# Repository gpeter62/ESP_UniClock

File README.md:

# ESP_UniClock v3.1

**A universal Wi-Fi clock firmware for ESP8266 / ESP32 — one codebase, 60+ different physical builds.**

Drive Nixie, VFD (vacuum fluorescent), Numitron, LED-segment, LED-matrix or NeoPixel "word clock"
displays from a single Arduino sketch. Which physical hardware you're building is selected entirely
in one file (`clocks.h`) — no code changes needed for a new build, just a new configuration block.

License: GPL-3.0-or-later (see the header of `ESP32_UniClock2.ino`) · Platforms: ESP8266, ESP32 ·
Language: C++ (Arduino)

---

## Table of contents

- [Features](#features)
- [Supported display drivers](#supported-display-drivers)
- [Optional components](#optional-components)
- [Screenshots](#screenshots)
- [Requirements](#requirements)
- [Getting started](#getting-started)
- [Configuration](#configuration-clocksh)
- [Developer documentation](#developer-documentation)
- [Schematics & PCB designs](#schematics--pcb-designs)
- [Manuals](#manuals)
- [External libraries](#external-libraries-bundled-in-libraries)
- [Known issues](#known-issues)
- [License](#license)
- [Author & support](#author--support)

---

## Features

- Works with any ESP8266 or ESP32 based module, via the Arduino IDE
- 1, 4, 6, 8 or 12 clock digits (tubes), depending on the build
- Time sync via Wi-Fi (NTP), GPS, or a DS3231 RTC chip — with automatic fallback between sources
- Wi-Fi in both infrastructure (STA) and standalone access-point (AP) modes, configured through a
  built-in responsive web UI (see [Screenshots](#screenshots))
- Temperature / humidity / barometric-pressure / ambient-light sensor support (see
  [Optional components](#optional-components))
- Adjustable day/night brightness, with optional automatic dimming from an ambient light sensor
- Radar or PIR motion sensor support to power tubes off when no one's around
- 8 tube-transition animation modes (including a random-pick mode)
- Full-color WS2812 (NeoPixel) tube backlighting with multiple animation effects
- Alarm function with buzzer and light
- Cathode/tube-life protection ("anti-poisoning") cycling
- Home Assistant integration via MQTT, including a master/slave mode so several clocks can share one
  physical sensor
- OTA firmware updates from the web UI
- Single-file hardware setup via `clocks.h` — no other source changes needed for a new physical build

## Supported display drivers

| Driver chip / scheme | Display type | Driver file(s) |
|---|---|---|
| SN74141 / 7441 / K155ID1 (BCD decoder), multiplexed | Nixie | `multiplex74141.ino` (8266), `multiplex74141_ESP32.ino` |
| SN74141, non-multiplexed (one decoder per tube) | Nixie | `no_multiplex74141.ino` (8266), `no_multiplex_ESP32.ino` |
| SN74141 + PCF8574 I²C port expander | Nixie | `pcf_multiplex74141.ino` |
| MAX6921 (20-ch. HV shift register) | VFD | `MAX6921.ino` (8266), `MAX6921_ESP32.ino` |
| HV5122 (32-ch. HV shift register, cascaded ×2) | Nixie | `HV5122new.ino` |
| PT6311 / PT6355 (smart VFD controller, on-chip scan) | VFD | `PT6311.ino`, `PT6355.ino` |
| SN75512 / SN75518 (HV shift register) | VFD | `SN75512.ino`, `SN75518.ino` |
| MM5450 (34-ch. LED driver) | LED 7-segment | `MM5450.ino` |
| MAX7219 / compatible | LED matrix / 7-segment | `MAX7219CNG.ino` |
| CD4511 / 74HC4511 (BCD→7-segment) | Numitron | `Numitron_4511N.ino` |
| 4× 74HC595 + optocouplers | Custom segment displays | `ZM1500.ino` |
| CD4543 + CD4028 (BCD→7-segment / BCD→decimal) | LED 7-segment | `mulev2.ino` ("Mule V2" board) |
| VQC10 (5×7 dot-matrix element) | Dot-matrix, full ASCII | `VQC10.ino` |
| WS2812 LED matrix behind an acrylic panel | "Word clock" (spells the time; EN/DE/HU) | `wordclock.ino` |
| — | Single-tube variant | `1tube.ino` |
| — | Sensor-only "clock" (no display) | `dummy.ino` |

Only one driver is compiled into any given firmware image — see [Configuration](#configuration-clocksh).

## Optional components

- DS18B20 temperature sensor (1 or 2 sensors on one bus)
- DHT11 / DHT22 temperature+humidity sensor
- BME280 / BMP280 / AHT10-AHT20 / SHT21 temperature/humidity/pressure sensor on I²C
- BH1750 ambient-light sensor on I²C
- Home Assistant integration via an MQTT client (with master/slave sensor sharing across clocks)
- DS3231 RTC module, settable via Wi-Fi or manually with pushbuttons
- Radar or PIR motion sensor
- GPS module for time sync in standalone (no-internet) setups
- WS2812 addressable LEDs for tube backlighting — fixed color or multiple animated effects
- Plain 3-pin PWM RGB backlighting (alternative to addressable LEDs, on boards with limited GPIO)
- User-defined GPIO pin numbers for every digit/segment/sensor/button

## Screenshots

- Web configuration UI: [`Webpage.jpg`](Webpage.jpg), [`Uniclock_v2 .png`](<Uniclock_v2 .png>)
- Photos of physical builds: [`photos/`](photos)
- PCB renders: [`PCB_available/`](PCB_available)

## Requirements

| Tool | Tested version |
|---|---|
| [Arduino IDE](https://www.arduino.cc/en/software) | **1.8.19** |
| ESP32 board package (`esp32` by Espressif Systems, via Boards Manager) | **2.0.17** |
| ESP8266 board package (`esp8266` by ESP8266 Community, via Boards Manager) | any recent 2.6.x–3.x (both are detected and handled at compile time, see `ESP32_UniClock2.ino`) |

> ⚠️ **Board package version matters.** This firmware has only been verified against **Arduino IDE
> 1.8.19** with the **ESP32 board package v2.0.17**. Newer Arduino IDE releases (2.x) or newer/older
> ESP32 core versions may require code changes (the ESP32 Arduino core's API — WiFi, LEDC/PWM, timer,
> and SPIFFS/LittleFS calls in particular — has changed across major versions). If you hit compile
> errors on a different toolchain version, try matching the tested versions above first before filing
> an issue.

## Getting started

1. **Download/clone this repository.**
2. **Install the libraries.** Unzip every archive in [`libraries/`](libraries) into your Arduino
   `libraries` folder (usually `Documents\Arduino\libraries` on Windows), **and rename this project's
   own folder to `ESP32_UniClock2`** — the sketch expects that exact folder name.
3. **Install the Boards Manager packages** for ESP8266 and/or ESP32 (see
   [Requirements](#requirements) for the tested versions).
4. **Pick (or write) your clock configuration** in [`clocks.h`](clocks.h) — see
   [Configuration](#configuration-clocksh) below.
5. **Select your board** in the Arduino IDE (`Tools → Board`) and the matching serial port.
6. **Upload the sketch** (`ESP32_UniClock2.ino`) as usual.
7. **Upload the web UI files to flash storage.** The files in [`data/`](data) (the config web page's
   HTML/CSS/JS) must be uploaded separately to SPIFFS/LittleFS using the filesystem-upload plugin —
   installers are bundled in [`SPIFFS uploaders/`](<SPIFFS uploaders>), or see:
   - [ESP8266 filesystem uploader tutorial](https://randomnerdtutorials.com/install-esp8266-filesystem-uploader-arduino-ide)
   - [ESP32 filesystem uploader tutorial](https://randomnerdtutorials.com/install-esp32-filesystem-uploader-arduino-ide)
8. **First boot**: if no Wi-Fi is configured, the clock starts its own access point (`192.168.4.1`) —
   connect to it and set your Wi-Fi/clock options from the web UI.

## Configuration (`clocks.h`)

All hardware setup lives in one file. Near the top, uncomment exactly **one** `#define CLOCK_NN` line
to select your build; every other line in that list must stay commented out. Each `CLOCK_NN` block then
defines the driver chip, GPIO pin assignments, and which optional features (sensors, RTC, GPS,
backlight, alarm, etc.) that specific build uses. To add a new physical build, copy the block closest
to your hardware, give it an unused number, and adjust the pins/options.

See [`docs/DEVELOPER_GUIDE.md`](docs/DEVELOPER_GUIDE.md) for the full breakdown of how `clocks.h`
drives the rest of the firmware.

## Developer documentation

This repository includes a full developer-documentation set (added during a 2026 code review pass):

- [`docs/DEVELOPER_GUIDE.md`](docs/DEVELOPER_GUIDE.md) — full architecture write-up: build model, the
  common driver interface, the core program's structure, the web admin API, and a complete driver catalog.
- [`docs/CODE_REVIEW.md`](docs/CODE_REVIEW.md) — file-by-file findings: bugs (fixed and open),
  optimization suggestions, and known limitations.
- [`docs/PROGRESS.md`](docs/PROGRESS.md) — status log of the review/documentation effort itself.

Every `.ino`/`.h` file in the project also has inline comments explaining the non-obvious hardware
protocol details, timing behavior, and known caveats of that specific driver.

## Schematics & PCB designs

See [`schematics/`](schematics) for KiCad-exported PCB/schematic PDFs, including:
- ESP32 clock, 6× IV-11 VFD tubes
- ESP32 clock, 6× Z573M/Z574M Nixie tubes
- ESP8266 Numitron clock, 4× IV-16 tubes
- ...and many more (ESP32 mainboard + interchangeable tube-driver daughterboards, HV5122-based flat
  panel builds, ESP8266 variants, etc.)

## Manuals

- UniClock Manual — English: [DOCX](<UniClock Manual ENG v3.1.docx>) · [PDF](<UniClock Manual ENG v3.1.pdf>)
- UniClock kézikönyv — Magyar: [DOCX](<UniClock Manual HUN v3.1.docx>) · [PDF](<UniClock Manual HUN v3.1.pdf>)

## External libraries (bundled in `libraries/`)

Core: `Time`, `Timezone`, `NTPClient`, `ESPAsyncWebServer`, `ESPAsyncTCP` (8266) / `AsyncTCP-ESP32`
(ESP32), `ESPAsyncWiFiManager`, `ArduinoJson`, `ESP32httpUpdate`, `EspSoftwareSerial`.

Optional (only needed for the sensors/features you enable): `Rtc_by_Makuna` (DS3231), `TinyGPSPlus`,
`NeoPixelBus_by_Makuna` (WS2812), `OneWire` + `DallasTemperature` (DS18B20), `DHT_sensor_library`,
`Adafruit_BME280_Library`, `Adafruit_BMP280_Library`, `Adafruit_AHTX0`, `Adafruit_BusIO`,
`Adafruit_Unified_Sensor`, `SHT21`, `BH1750`, `PubSubClient` + `arduino-home-assistant` (MQTT/Home
Assistant), `Samsung_16LF01_VFD`.

## Known issues

See [`docs/CODE_REVIEW.md`](docs/CODE_REVIEW.md) for the complete, current list. Most notably:
`mqtt.ino` ships a hardcoded default MQTT broker address/username/password (set in `factoryReset()`)
and had a buffer-handling issue in incoming-message parsing — **change the MQTT credentials from the
web UI before exposing an MQTT-enabled build to an untrusted network**, and see the code review for
details before relying on it in a security-sensitive setup.

## License

Released under the **GNU General Public License v3 (or later)** — see the license header in
`ESP32_UniClock2.ino` for the full notice.

## Author & support

**Peter Gautier** — [gautier.p62@gmail.com](mailto:gautier.p62@gmail.com)

Before uploading to the ESP board, don't forget to unzip the library files into the Arduino IDE's
`libraries` folder and **rename this project's own folder to `ESP32_UniClock2`**.

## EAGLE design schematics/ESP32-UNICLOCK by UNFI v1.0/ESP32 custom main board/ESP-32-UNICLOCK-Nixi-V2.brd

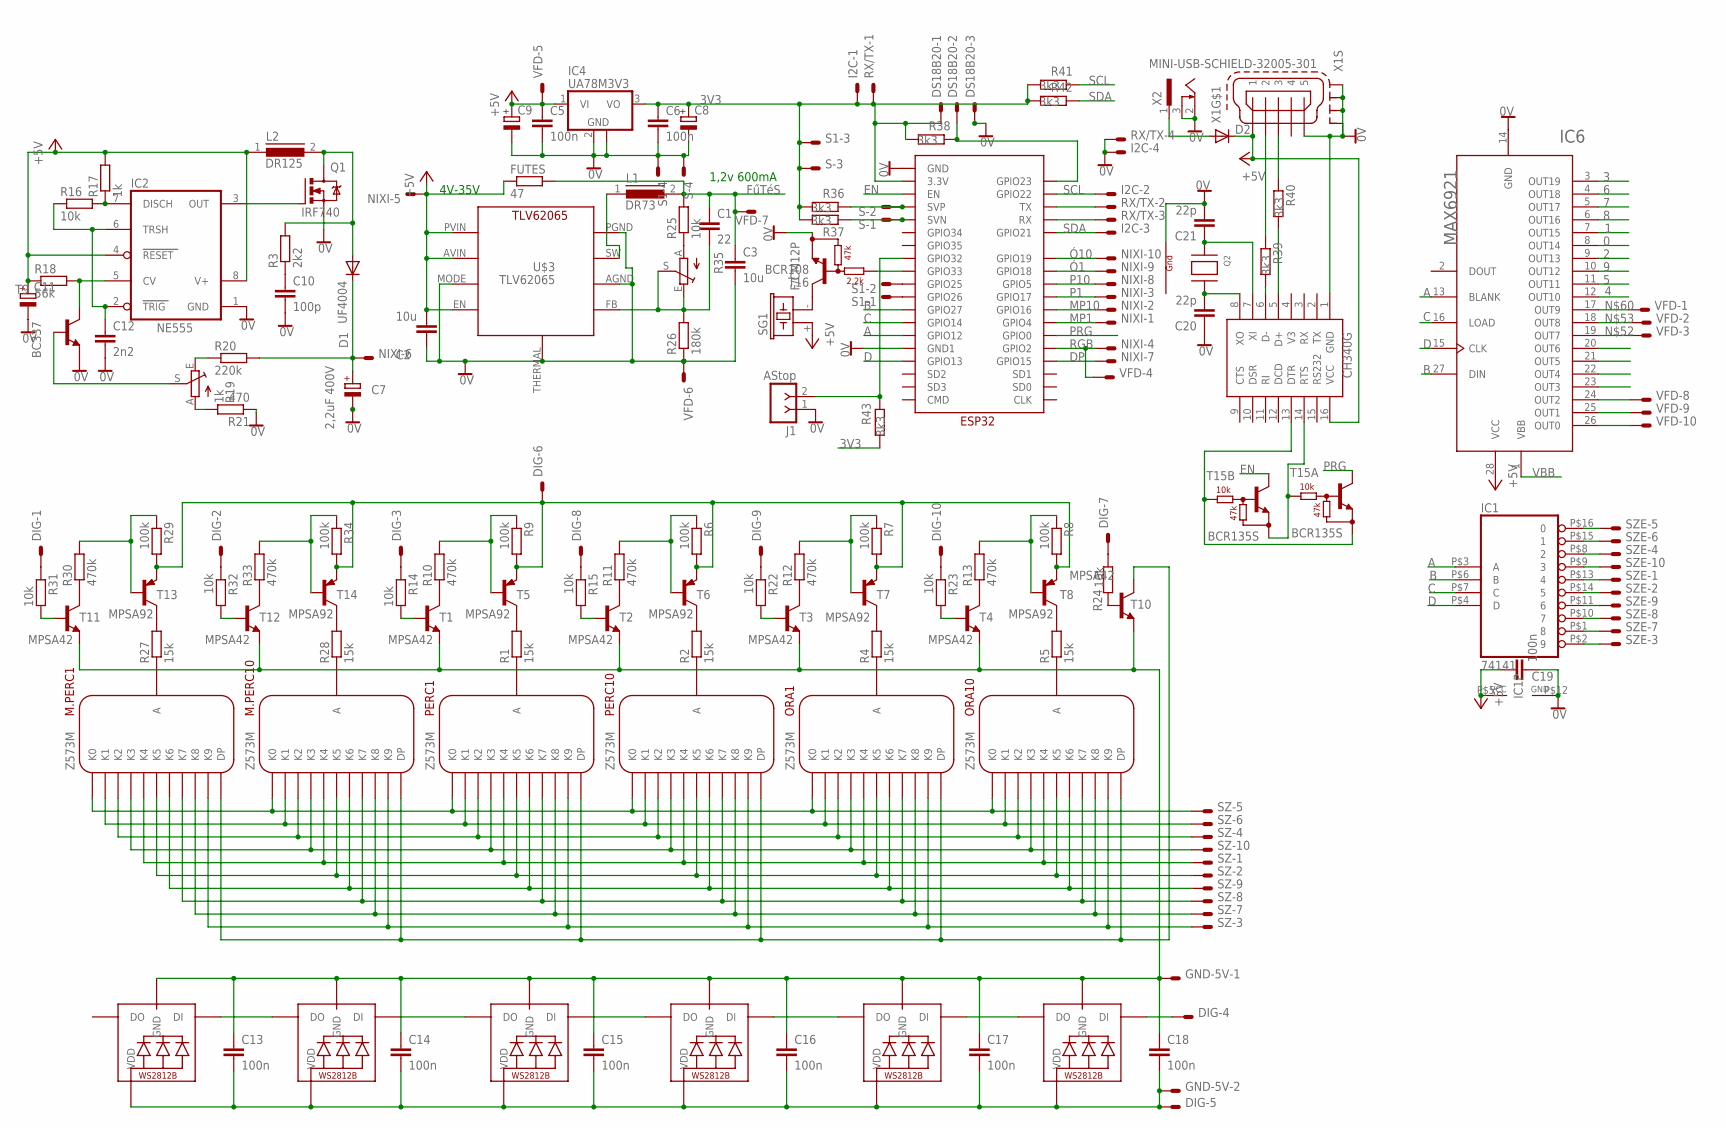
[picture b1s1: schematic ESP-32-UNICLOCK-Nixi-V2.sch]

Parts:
C1: 22; 0603
C2, C3: 10u; 1206
C5, C6, C19: 100n; 0603
C7: 2,2uF 400V; E2,5-7
C8, C9: CPOL-EUE2.5-5; E2,5-5
C10: 100p; C050-024X044
C11: CPOL-EUE2.5-7; E2,5-7
C12: 2n2; C0603
C13, C14, C15, C16, C17, C18: 100n; C0603
C20, C21: 22p; 0603
D1: UF4004; DO35-10
D2: DIODE-SOD123; SOD123
DIG: DIG; PAD10
DS18B20: PAD3
FUTES: 47; 0207/10
GND-5V: PAD2
I2C: PAD4
IC1: 74141; DIL16SMD
IC2: NE555; DIL08
IC4: UA78M3V3; SOT223
IC6: MAX6921; SO-28W
J1: AStop; SIP-100-02-32
L1: DR73
L2: DR125
LED1, LED2, LED3, LED4, LED5, LED6: WS2812B_5050N; WS2812B-NARROW
M.PERC1: MP1; Z573SZ1
M.PERC10: MP10; Z573SZ1
NIXI: PAD10
ORA1: O1; Z573SZ1
ORA10: O10; Z573SZ1
PERC1: P1; Z573SZ1
PERC10: P10; Z573SZ1
Q1: IRF740; TO220BV
Q2: XTAL-4-3225; NX3225
R1, R2, R4, R5, R27, R28: 15k; 0207/7
R3: 2k2; 0204/7
R6, R7, R8, R9, R29, R34: 100k; 0207/7
R10, R11, R12, R13, R30, R33: 470k; 0207/7
R14, R15, R22, R23, R24, R31, R32: 10k; 0207/7
R16: 10k; R0603
R17: 1k; R0603
R18: 56k; R0603
R19: 1k; CA6H
R20: 220k; 0204/7
R21: 470; 0204/7
R25: 10k; 0603
R26: 180k; 0603
R35: TRIM_EU-B25P; B25P
R36, R37, R38, R39, R40, R41, R42, R43: 3k3; 0603
RX/TX: PAD4
S, S1: PAD4
SG1: F/CM12P
SZ: PAD10
SZE: PAD10
T1, T2, T3, T4, T10, T11, T12: MPSA42; TO92-EBC
T5, T6, T7, T8, T13, T14: MPSA92; TO92-EBC
T9: BC337; TO92-CBE
T15: BCR135S; SOT363_INFINEON
T16: BCR108; SOT23-BEC
U$1: CH340G; SOIC16
U$2: ESP32-2X18; ESP322X18
U$3: TLV62065
VFD: PAD10
X1: MINI-USB-SCHIELD-32005-301; 32005-301
X2: 733989-5

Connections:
0: IC1.P$16 (0), IC6.8 (OUT14), SZE.P$5
0V: C2.2, C3.2, C5.2, C6.2, C7.-, C8.-, C9.-, C10.2, C11.-, C12.2, C19.2, C20.1, C21.2, DS18B20.P$3, I2C.P$4, IC1.P$12 (GND), IC2.1 (GND), IC4.2 (GND), IC4.4 (GND), IC6.14 (GND), J1.1, Q1.S, Q2.4 (G1), R21.1, R26.1, RX/TX.P$4, S.P$4, S1.P$4, T9.E, T16.E, U$1.1 (GND), U$2.P$19 (GND), U$2.P$26 (GND1), U$3.AGND, U$3.MODE, U$3.PGND, U$3.THERMAL, VFD.P$6, X1.5, X1.M1 (S1), X1.M2 (S2), X1.M3 (S3), X1.M4 (S4), X2.2, X2.3
1: IC1.P$15 (1), IC6.7 (OUT15), SZE.P$6
2: IC1.P$8 (2), IC6.9 (OUT13), SZE.P$4
3: IC1.P$9 (3), IC6.3 (OUT19), SZE.P$10
3V3: C6.1, C8.+, DS18B20.P$1, I2C.P$1, IC4.3 (VO), R36.2, R37.2, R38.2, R41.2, R42.2, R43.2, RX/TX.P$1, S.P$3, S1.P$3, U$2.P$20 (3.3V)
4: IC1.P$13 (4), IC6.12 (OUT10), SZE.P$1
5: IC1.P$14 (5), IC6.11 (OUT11), SZE.P$2
6: IC1.P$11 (6), IC6.4 (OUT18), SZE.P$9
7: IC1.P$10 (7), IC6.5 (OUT17), SZE.P$8
8: IC1.P$1 (8), IC6.6 (OUT16), SZE.P$7
9: IC1.P$2 (9), IC6.10 (OUT12), SZE.P$3
+5V: C2.1, C5.1, C9.+, C11.+, C19.1, D2.C, FUTES.1, IC1.P$5 (VCC), IC2.4 (RESET), IC2.8 (V+), IC4.1 (VI), IC6.28 (VCC), L2.1, NIXI.P$5, R17.2, R18.1, SG1.+ (1), U$1.16 (VCC), U$3.AVIN, U$3.EN, U$3.PVIN, VFD.P$5, X1.1
A: IC1.P$3 (A), IC6.13 (BLANK), U$2.P$12 (GPIO12)
B: IC1.P$6 (B), IC6.27 (DIN), U$2.P$10 (GPIO27)
C: IC1.P$7 (C), IC6.16 (LOAD), U$2.P$9 (GPIO14)
D: IC1.P$4 (D), IC6.15 (CLK), U$2.P$11 (GPIO13)
DP: NIXI.P$7, U$2.P$35 (GPIO15)
EN: T15.3 (C), U$2.P$21 (EN)
FűTéS: C1.1, C3.1, FUTES.2, L1.2, R25.2, VFD.P$7
G2: Q2.2 (G2)
GND1: C13.1, C14.1, C15.1, C16.1, C17.1, C18.1, GND-5V.P$1, LED1.3-GND (GND), LED2.3-GND (GND), LED3.3-GND (GND), LED4.3-GND (GND), LED5.3-GND (GND), LED6.3-GND (GND), T1.E, T2.E, T3.E, T4.E, T10.E, T11.E, T12.E
MP1: NIXI.P$1, U$2.P$34 (GPIO4)
MP10: NIXI.P$2, U$2.P$31 (GPIO16)
unnamed: T15.1 (E), T15.5 (B), U$1.13 (DTR)
unnamed: S1.P$1, U$2.P$7 (GPIO26)
unnamed: IC6.26 (OUT0), VFD.P$10
unnamed: IC6.25 (OUT1), VFD.P$9
unnamed: L1.1, U$3.SW
unnamed: IC6.24 (OUT2), VFD.P$8
unnamed: PERC1.A, R1.1
unnamed: PERC10.A, R2.1
unnamed: ORA1.A, R4.1
unnamed: ORA10.A, R5.1
unnamed: R1.2, T5.C
unnamed: R2.2, T6.C
unnamed: R4.2, T7.C
unnamed: R5.2, T8.C
unnamed: R19.E, R20.1
unnamed: R10.1, T1.C
unnamed: R19.A, R21.2
unnamed: R9.1, R10.2, T5.B
unnamed: IC2.3 (OUT), Q1.G
unnamed: IC2.7 (DISCH), R16.2, R17.1
unnamed: C12.1, IC2.2 (TRIG), IC2.6 (TRSH), R16.1
unnamed: R6.1, R11.2, T6.B
unnamed: IC2.5 (CV), R18.2, T9.C
unnamed: C10.1, R3.1
unnamed: R37.1, S.P$1, U$2.P$1 (SVN)
unnamed: R7.1, R12.2, T7.B
unnamed: R8.1, R13.2, T8.B
unnamed: R11.1, T2.C
unnamed: R12.1, T3.C
unnamed: R13.1, T4.C
unnamed: R14.2, T1.B
unnamed: R15.2, T2.B
unnamed: R22.2, T3.B
unnamed: R23.2, T4.B
unnamed: R24.2, T10.B
unnamed: DIG.P$1, R31.1
unnamed: DIG.P$6, R6.2, R7.2, R8.2, R9.2, R29.2, R34.2, T5.E, T6.E, T7.E, T8.E, T13.E, T14.E
unnamed: DIG.P$2, R32.1
unnamed: M.PERC1.K0, M.PERC10.K0, ORA1.K0, ORA10.K0, PERC1.K0, PERC10.K0, SZ.P$5
unnamed: D1.A, L2.2, Q1.D, R3.2
unnamed: M.PERC1.K1, M.PERC10.K1, ORA1.K1, ORA10.K1, PERC1.K1, PERC10.K1, SZ.P$6
unnamed: DS18B20.P$2, R38.1, U$2.P$23 (GPIO23)
unnamed: DIG.P$8, R15.1
unnamed: DIG.P$10, R23.1
unnamed: IC6.19 (OUT7), VFD.P$3
unnamed: IC6.18 (OUT8), VFD.P$2
unnamed: LED1.2-DOUT (DO), LED2.4-DIN (DI)
unnamed: LED2.2-DOUT (DO), LED3.4-DIN (DI)
unnamed: M.PERC1.K2, M.PERC10.K2, ORA1.K2, ORA10.K2, PERC1.K2, PERC10.K2, SZ.P$4
unnamed: M.PERC1.K3, M.PERC10.K3, ORA1.K3, ORA10.K3, PERC1.K3, PERC10.K3, SZ.P$10
unnamed: M.PERC1.K4, M.PERC10.K4, ORA1.K4, ORA10.K4, PERC1.K4, PERC10.K4, SZ.P$1
unnamed: M.PERC1.K5, M.PERC10.K5, ORA1.K5, ORA10.K5, PERC1.K5, PERC10.K5, SZ.P$2
unnamed: IC6.17 (OUT9), VFD.P$1
unnamed: M.PERC1.K6, M.PERC10.K6, ORA1.K6, ORA10.K6, PERC1.K6, PERC10.K6, SZ.P$9
unnamed: M.PERC1.K7, M.PERC10.K7, ORA1.K7, ORA10.K7, PERC1.K7, PERC10.K7, SZ.P$8
unnamed: M.PERC1.K8, M.PERC10.K8, ORA1.K8, ORA10.K8, PERC1.K8, PERC10.K8, SZ.P$7
unnamed: M.PERC1.K9, M.PERC10.K9, ORA1.K9, ORA10.K9, PERC1.K9, PERC10.K9, SZ.P$3
unnamed: LED3.2-DOUT (DO), LED4.4-DIN (DI)
unnamed: LED4.2-DOUT (DO), LED5.4-DIN (DI)
unnamed: DIG.P$9, R22.1
unnamed: DIG.P$7, R24.1
unnamed: DIG.P$3, R14.1
unnamed: D2.A, X2.1
unnamed: DIG.P$4, LED1.4-DIN (DI)
unnamed: R36.1, S.P$2, U$2.P$2 (SVP)
unnamed: S1.P$2, U$2.P$8 (GPIO25)
unnamed: R39.1, X1.2
unnamed: R40.2, U$1.5 (D+)
unnamed: R39.2, U$1.6 (D-)
unnamed: R40.1, X1.3
unnamed: LED5.2-DOUT (DO), LED6.4-DIN (DI)
unnamed: T15.2 (B), T15.4 (E), U$1.14 (RTS)
unnamed: C20.2, Q2.3 (X2), U$1.8 (XO)
unnamed: C13.2, C14.2, C15.2, C16.2, C17.2, C18.2, DIG.P$5, GND-5V.P$2, LED1.1-VDD (VDD), LED2.1-VDD (VDD), LED3.1-VDD (VDD), LED4.1-VDD (VDD), LED5.1-VDD (VDD), LED6.1-VDD (VDD)
unnamed: M.PERC1.A, R27.1
unnamed: M.PERC10.A, R28.1
unnamed: R27.2, T13.C
unnamed: R28.2, T14.C
unnamed: R30.1, T11.C
unnamed: R31.2, T11.B
unnamed: R32.2, T12.B
unnamed: C21.1, Q2.1 (X1), U$1.7 (XI)
unnamed: R29.1, R30.2, T13.B
unnamed: R33.2, R34.1, T14.B
unnamed: RX/TX.P$2, U$2.P$22 (TX)
unnamed: RX/TX.P$3, U$2.P$24 (RX)
unnamed: SG1.- (2), T16.C
unnamed: T16.B, U$2.P$5 (GPIO33)
unnamed: J1.2, R43.1, U$2.P$6 (GPIO32)
unnamed: R25.1, R35.A
unnamed: C1.2, R26.2, R35.E, R35.S, U$3.FB
unnamed: R33.1, T12.C
unnamed: M.PERC1.DP, M.PERC10.DP, ORA1.DP, ORA10.DP, PERC1.DP, PERC10.DP, T10.C
unnamed: R19.S, T9.B
P1: NIXI.P$3, U$2.P$32 (GPIO17)
P10: NIXI.P$8, U$2.P$29 (GPIO5)
PRG: T15.6 (C), U$2.P$33 (GPIO0)
RGB: NIXI.P$4, U$2.P$36 (GPIO2), VFD.P$4
SCL: I2C.P$2, R41.1, U$2.P$25 (GPIO22)
SDA: I2C.P$3, R42.1, U$2.P$28 (GPIO21)
VBB: C7.+, D1.C, IC6.1 (VBB), NIXI.P$6, R20.2
Ó1: NIXI.P$9, U$2.P$30 (GPIO18)
Ó10: NIXI.P$10, U$2.P$27 (GPIO19)

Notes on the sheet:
4V-35V
1,2v 600mA

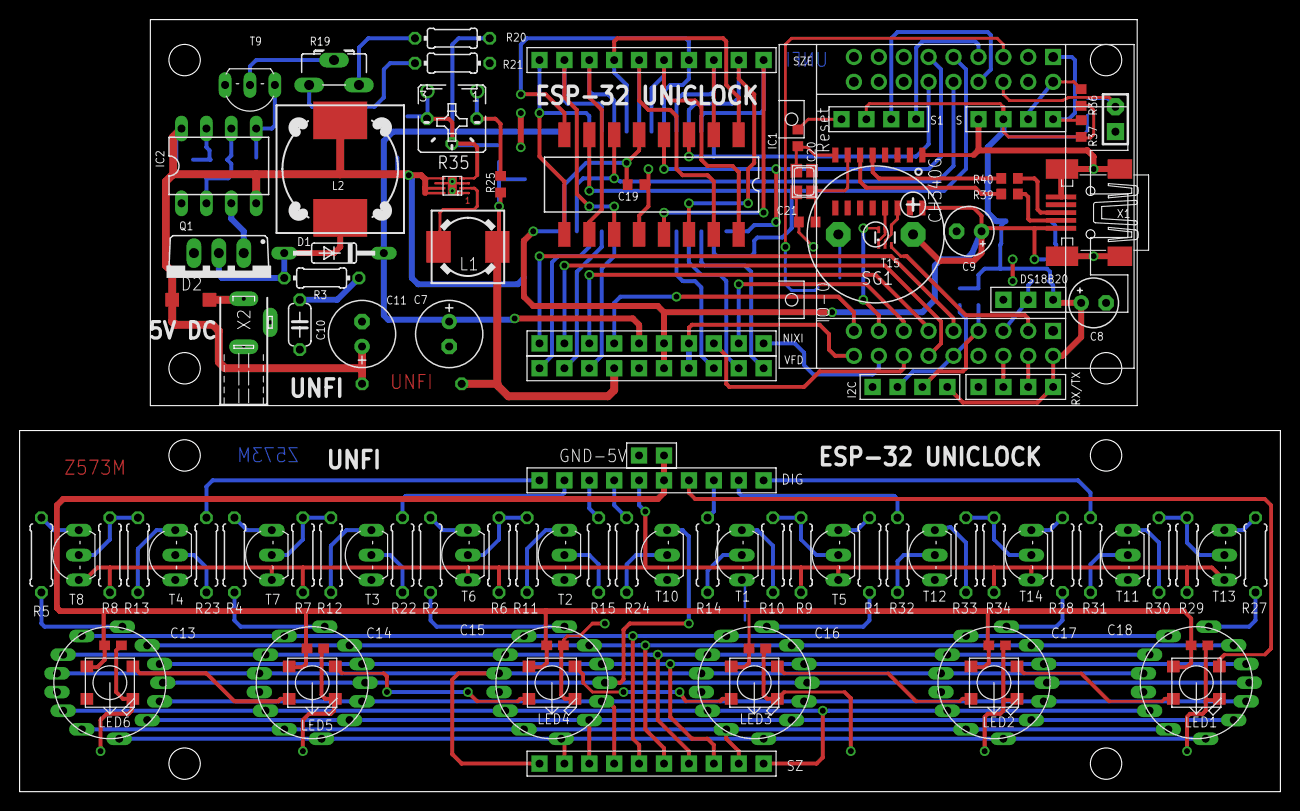
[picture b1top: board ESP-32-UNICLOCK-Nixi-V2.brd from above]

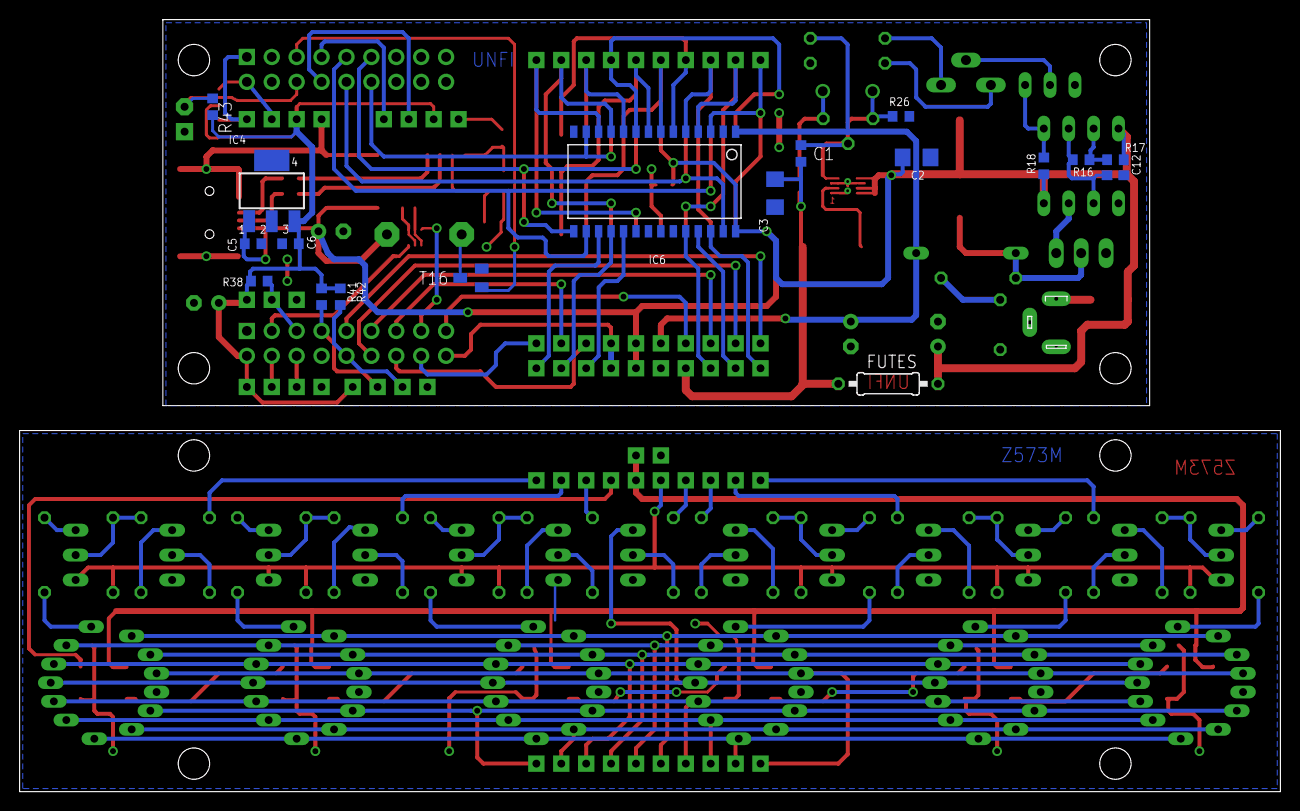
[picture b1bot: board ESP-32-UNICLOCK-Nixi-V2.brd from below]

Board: 2 copper layers, 128.6 x 78.7 mm, 120 parts (18 on the bottom side), 126 nets.

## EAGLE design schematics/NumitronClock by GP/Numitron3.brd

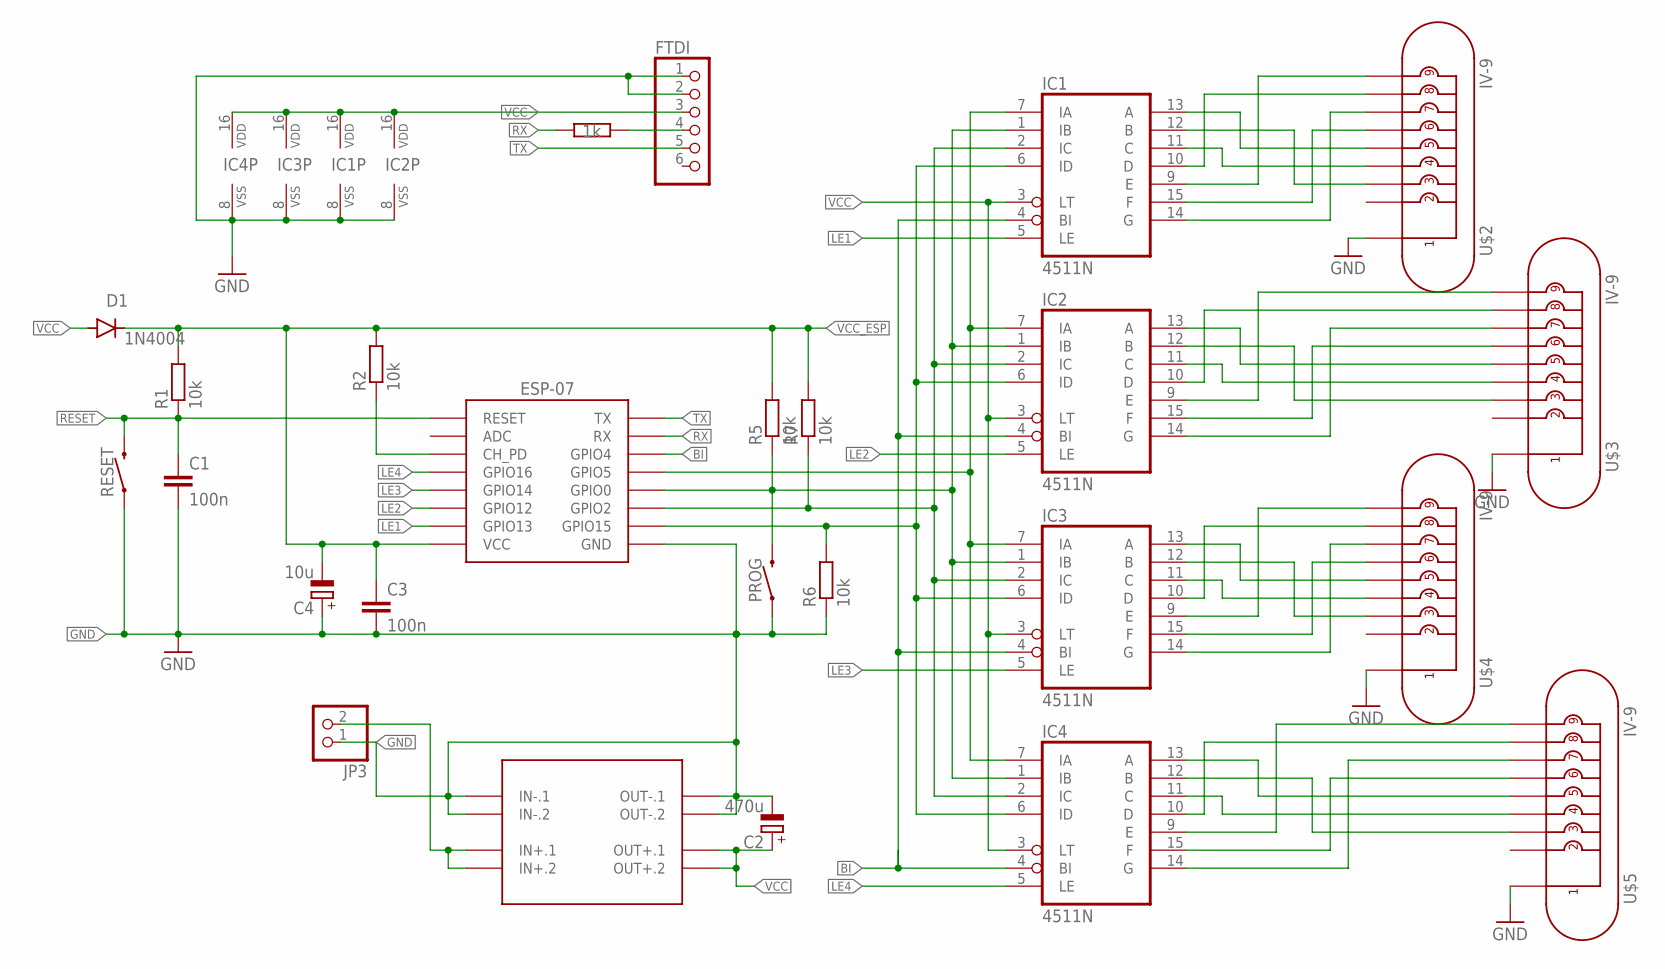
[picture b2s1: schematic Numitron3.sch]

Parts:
C1: 100n; C025-024X044
C2: 470u; B45181B
C3: 100n; C025-050X050
C4: 10u; B45181A
D1: 1N4004; DO41-10
ESP-07: ESP12SMD; ESP12-SMD
FTDI: PINHD-1X6; 1X06
IC1, IC2, IC3, IC4: 4511N; DIL16
JP3: PINHD-1X2; 1X02
PROG: MOMENTARY-SWITCH-SPST-PTH-6.0MM; TACTILE_SWITCH_PTH_6.0MM
R1, R2, R5, R6, R7: 10k; 0204/7
R4: 1k; 0204/7
RESET: MOMENTARY-SWITCH-SPST-PTH-6.0MM; TACTILE_SWITCH_PTH_6.0MM
U$2, U$3, U$4, U$5: IV-9
U$6: DC-DC-STEP-DOWN-MP1584

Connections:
BI: ESP-07.GPIO4, IC1.4 (BI), IC2.4 (BI), IC3.4 (BI), IC4.4 (BI)
GND: C1.2, C2.-, C3.2, C4.+, ESP-07.GND, FTDI.1, FTDI.2, IC1.8 (VSS), IC2.8 (VSS), IC3.8 (VSS), IC4.8 (VSS), JP3.1, PROG.1, R6.1, RESET.1, U$2.1, U$3.1, U$4.1, U$5.1, U$6.IN-.1, U$6.IN-.2, U$6.OUT-.1, U$6.OUT-.2
LE1: ESP-07.GPIO13, IC1.5 (LE)
LE2: ESP-07.GPIO12, IC2.5 (LE)
LE3: ESP-07.GPIO14, IC3.5 (LE)
LE4: ESP-07.GPIO16, IC4.5 (LE)
unnamed: ESP-07.GPIO5, IC1.7 (IA), IC2.7 (IA), IC3.7 (IA), IC4.7 (IA)
unnamed: ESP-07.GPIO0, IC1.1 (IB), IC2.1 (IB), IC3.1 (IB), IC4.1 (IB), PROG.3 (2), R5.1
unnamed: ESP-07.GPIO2, IC1.2 (IC), IC2.2 (IC), IC3.2 (IC), IC4.2 (IC), R7.1
unnamed: ESP-07.GPIO15, IC1.6 (ID), IC2.6 (ID), IC3.6 (ID), IC4.6 (ID), R6.2
unnamed: IC1.13 (A), U$2.5
unnamed: IC1.12 (B), U$2.3
unnamed: IC1.11 (C), U$2.4
unnamed: IC1.10 (D), U$2.8
unnamed: IC1.9 (E), U$2.9
unnamed: IC1.15 (F), U$2.6
unnamed: IC1.14 (G), U$2.7
unnamed: IC2.14 (G), U$3.7
unnamed: IC2.12 (B), U$3.3
unnamed: IC2.13 (A), U$3.5
unnamed: IC2.10 (D), U$3.8
unnamed: IC2.9 (E), U$3.9
unnamed: IC2.11 (C), U$3.4
unnamed: IC2.15 (F), U$3.6
unnamed: IC3.9 (E), U$4.9
unnamed: IC3.13 (A), U$4.5
unnamed: IC3.12 (B), U$4.3
unnamed: IC3.15 (F), U$4.6
unnamed: IC3.14 (G), U$4.7
unnamed: IC3.10 (D), U$4.8
unnamed: IC3.11 (C), U$4.4
unnamed: IC4.14 (G), U$5.7
unnamed: IC4.15 (F), U$5.6
unnamed: IC4.9 (E), U$5.9
unnamed: IC4.10 (D), U$5.8
unnamed: IC4.11 (C), U$5.4
unnamed: IC4.12 (B), U$5.3
unnamed: IC4.13 (A), U$5.5
unnamed: ESP-07.CH_PD, R2.1
unnamed: JP3.2, U$6.IN+.1, U$6.IN+.2
unnamed: FTDI.4, R4.1
RESET: C1.1, ESP-07.RESET, R1.1, RESET.3 (2)
RX: ESP-07.RXD0 (RX), R4.2
TX: ESP-07.TXD0 (TX), FTDI.5
VCC: C2.+, D1.A, FTDI.3, IC1.3 (LT), IC1.16 (VDD), IC2.3 (LT), IC2.16 (VDD), IC3.3 (LT), IC3.16 (VDD), IC4.3 (LT), IC4.16 (VDD), U$6.OUT+.1, U$6.OUT+.2
VCC_ESP: C3.1, C4.-, D1.C, ESP-07.VCC, R1.2, R2.2, R5.2, R7.2

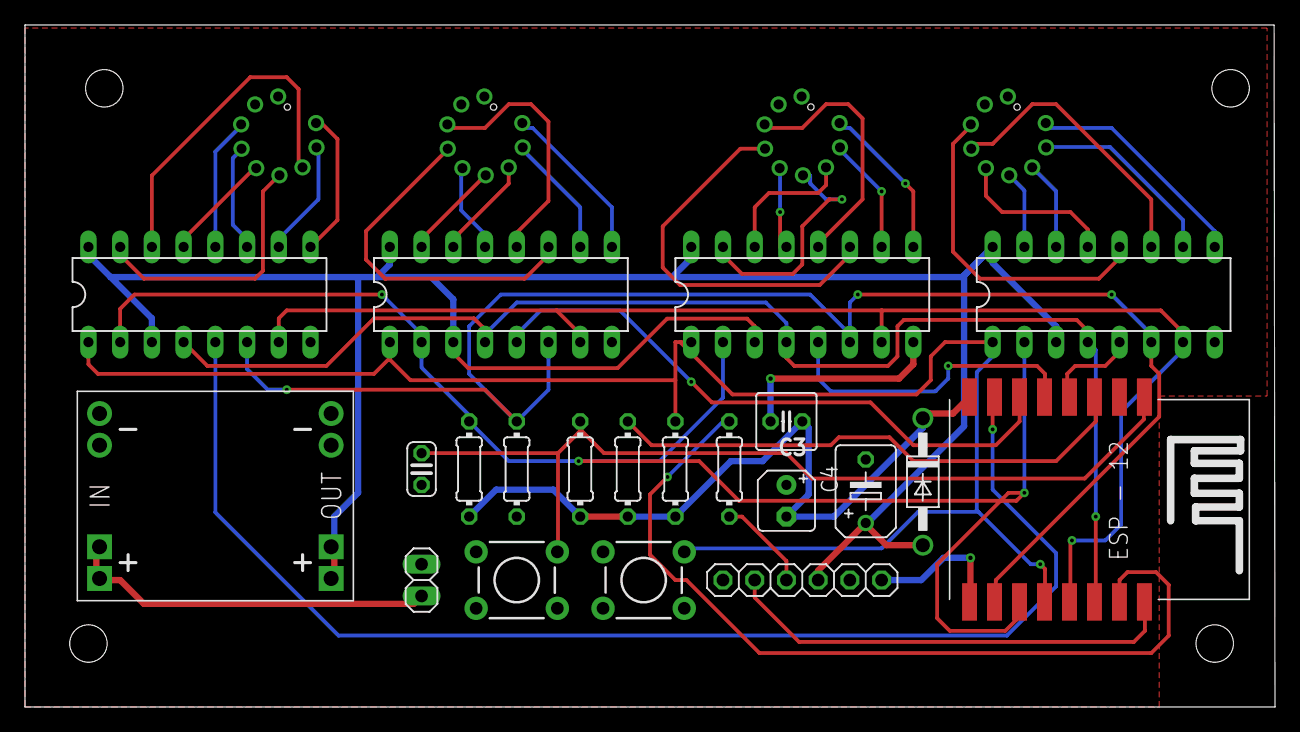
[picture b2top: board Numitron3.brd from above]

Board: 2 copper layers, 100.1 x 54.6 mm, 25 parts (0 on the bottom side), 46 nets.

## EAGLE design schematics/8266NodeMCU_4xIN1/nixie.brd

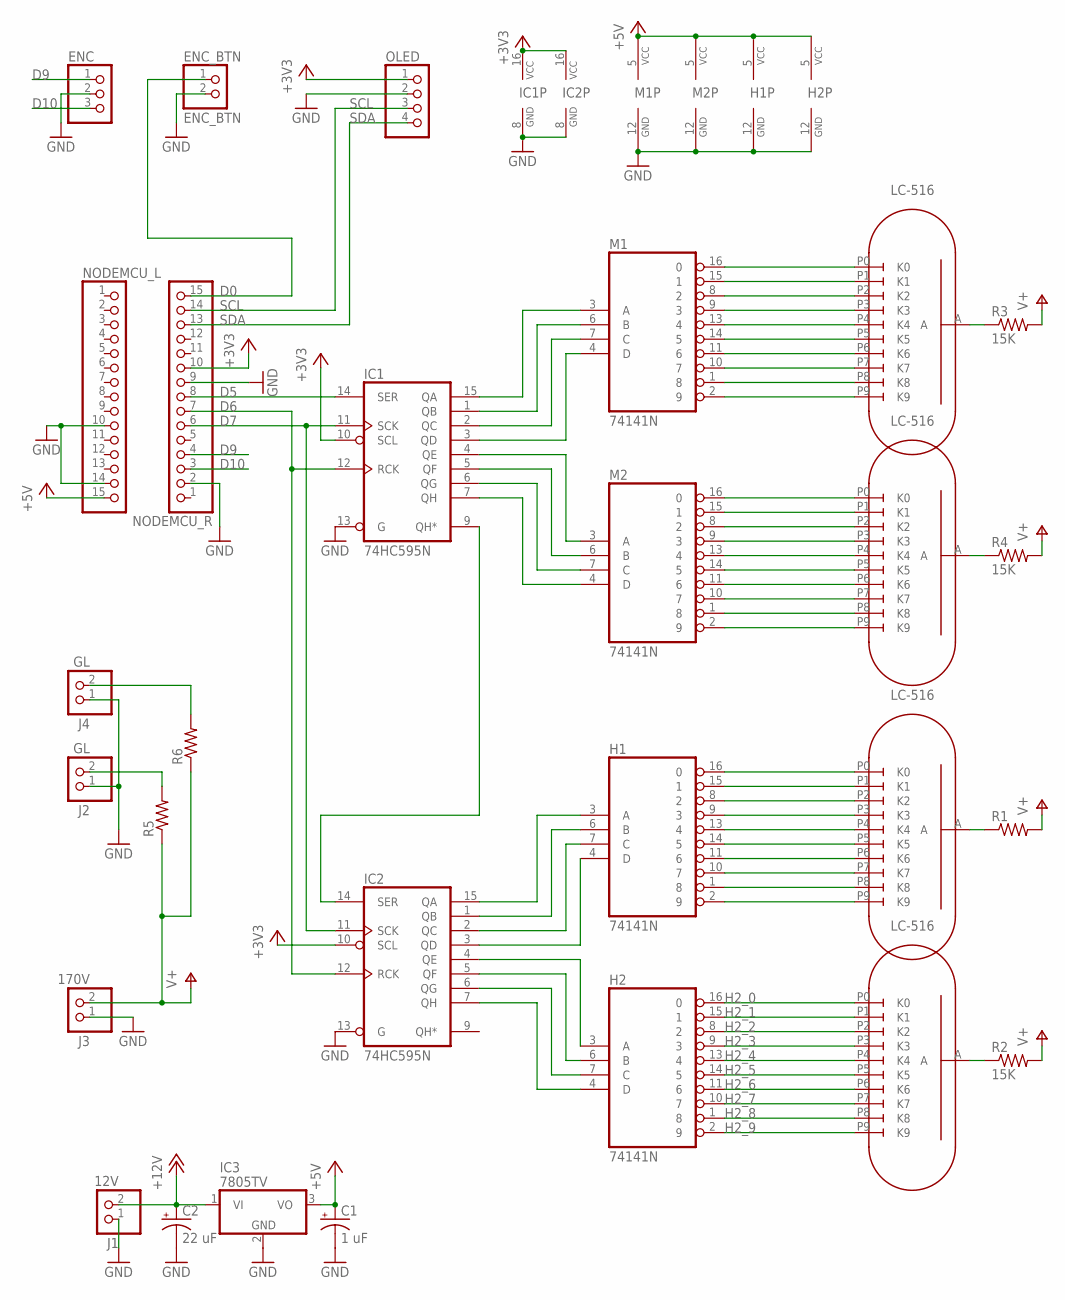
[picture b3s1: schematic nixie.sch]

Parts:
C1: 1 uF; TT2D5
C2: 22 uF; TT2D5
ENC: PINHD-1X3; 1X03
ENC_BTN: ENC_BTN; 1X02
H1, H2: 74141N; DIL16
IC1, IC2: 74HC595N; DIL16
IC3: 7805TV; TO220V
J1: 12V; 1X02
J2, J4: GL; 1X02
J3: 170V; 1X02
M1, M2: 74141N; DIL16
NODEMCU_L: PINHD-1X15; 1X15
NODEMCU_R: PINHD-1X15; 1X15
OLED: PINHD-1X4; 1X04
R1, R2, R3, R4: 15K; 0207/10
R5, R6: 100k; 0207/10
U$1M2, U$2M1, U$3H2, U$4H1: LC-516

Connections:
+3V3: IC1.10 (SCL), IC1.16 (VCC), IC2.10 (SCL), IC2.16 (VCC), NODEMCU_R.10, OLED.1
+5V: C1.+, H1.5 (VCC), H2.5 (VCC), IC3.3 (VO), M1.5 (VCC), M2.5 (VCC), NODEMCU_L.15
+12V: C2.+, IC3.1 (VI), J1.2
D0: ENC_BTN.1, NODEMCU_R.15
D5: IC1.14 (SER), NODEMCU_R.8
D6: IC1.12 (RCK), IC2.12 (RCK), NODEMCU_R.7
D7: IC1.11 (SCK), IC2.11 (SCK), NODEMCU_R.6
D9: ENC.1, NODEMCU_R.4
D10: ENC.3, NODEMCU_R.3
GND: C1.-, C2.-, ENC.2, ENC_BTN.2, H1.12 (GND), H2.12 (GND), IC1.8 (GND), IC1.13 (G), IC2.8 (GND), IC2.13 (G), IC3.2 (GND), J1.1, J2.1, J3.1, J4.1, M1.12 (GND), M2.12 (GND), NODEMCU_L.10, NODEMCU_L.14, NODEMCU_R.2, NODEMCU_R.9, OLED.2
H2_0: H2.16 (0), U$4H1.P0 (K0)
H2_1: H2.15 (1), U$4H1.P1 (K1)
H2_2: H2.8 (2), U$4H1.P2 (K2)
H2_3: H2.9 (3), U$4H1.P3 (K3)
H2_4: H2.13 (4), U$4H1.P4 (K4)
H2_5: H2.14 (5), U$4H1.P5 (K5)
H2_6: H2.11 (6), U$4H1.P6 (K6)
H2_7: H2.10 (7), U$4H1.P7 (K7)
H2_8: H2.1 (8), U$4H1.P8 (K8)
H2_9: H2.2 (9), U$4H1.P9 (K9)
unnamed: H1.16 (0), U$3H2.P0 (K0)
unnamed: H1.2 (9), U$3H2.P9 (K9)
unnamed: H1.9 (3), U$3H2.P3 (K3)
unnamed: H1.13 (4), U$3H2.P4 (K4)
unnamed: H1.14 (5), U$3H2.P5 (K5)
unnamed: H1.11 (6), U$3H2.P6 (K6)
unnamed: H1.10 (7), U$3H2.P7 (K7)
unnamed: H1.1 (8), U$3H2.P8 (K8)
unnamed: H1.8 (2), U$3H2.P2 (K2)
unnamed: H1.15 (1), U$3H2.P1 (K1)
unnamed: R1.1, U$3H2.A
unnamed: J4.2, R6.2
unnamed: J2.2, R5.2
unnamed: R2.1, U$4H1.A
unnamed: M1.16 (0), U$1M2.P0 (K0)
unnamed: M1.9 (3), U$1M2.P3 (K3)
unnamed: M1.13 (4), U$1M2.P4 (K4)
unnamed: M1.14 (5), U$1M2.P5 (K5)
unnamed: M1.11 (6), U$1M2.P6 (K6)
unnamed: M1.10 (7), U$1M2.P7 (K7)
unnamed: M1.1 (8), U$1M2.P8 (K8)
unnamed: M1.2 (9), U$1M2.P9 (K9)
unnamed: M1.8 (2), U$1M2.P2 (K2)
unnamed: M1.15 (1), U$1M2.P1 (K1)
unnamed: R3.1, U$1M2.A
unnamed: M2.16 (0), U$2M1.P0 (K0)
unnamed: M2.9 (3), U$2M1.P3 (K3)
unnamed: M2.13 (4), U$2M1.P4 (K4)
unnamed: M2.14 (5), U$2M1.P5 (K5)
unnamed: M2.11 (6), U$2M1.P6 (K6)
unnamed: M2.10 (7), U$2M1.P7 (K7)
unnamed: M2.1 (8), U$2M1.P8 (K8)
unnamed: M2.2 (9), U$2M1.P9 (K9)
unnamed: M2.8 (2), U$2M1.P2 (K2)
unnamed: M2.15 (1), U$2M1.P1 (K1)
unnamed: R4.1, U$2M1.A
unnamed: IC1.15 (QA), M1.3 (A)
unnamed: IC1.1 (QB), M1.6 (B)
unnamed: IC1.2 (QC), M1.7 (C)
unnamed: IC1.3 (QD), M1.4 (D)
unnamed: IC1.4 (QE), M2.3 (A)
unnamed: IC1.5 (QF), M2.6 (B)
unnamed: IC1.6 (QG), M2.7 (C)
unnamed: IC1.7 (QH), M2.4 (D)
unnamed: H1.3 (A), IC2.15 (QA)
unnamed: H1.6 (B), IC2.1 (QB)
unnamed: H1.7 (C), IC2.2 (QC)
unnamed: H1.4 (D), IC2.3 (QD)
unnamed: H2.3 (A), IC2.4 (QE)
unnamed: H2.6 (B), IC2.5 (QF)
unnamed: H2.7 (C), IC2.6 (QG)
unnamed: H2.4 (D), IC2.7 (QH)
unnamed: IC1.9 (QH*), IC2.14 (SER)
SCL: NODEMCU_R.14, OLED.3
SDA: NODEMCU_R.13, OLED.4
V+: J3.2, R1.2, R2.2, R3.2, R4.2, R5.1, R6.1

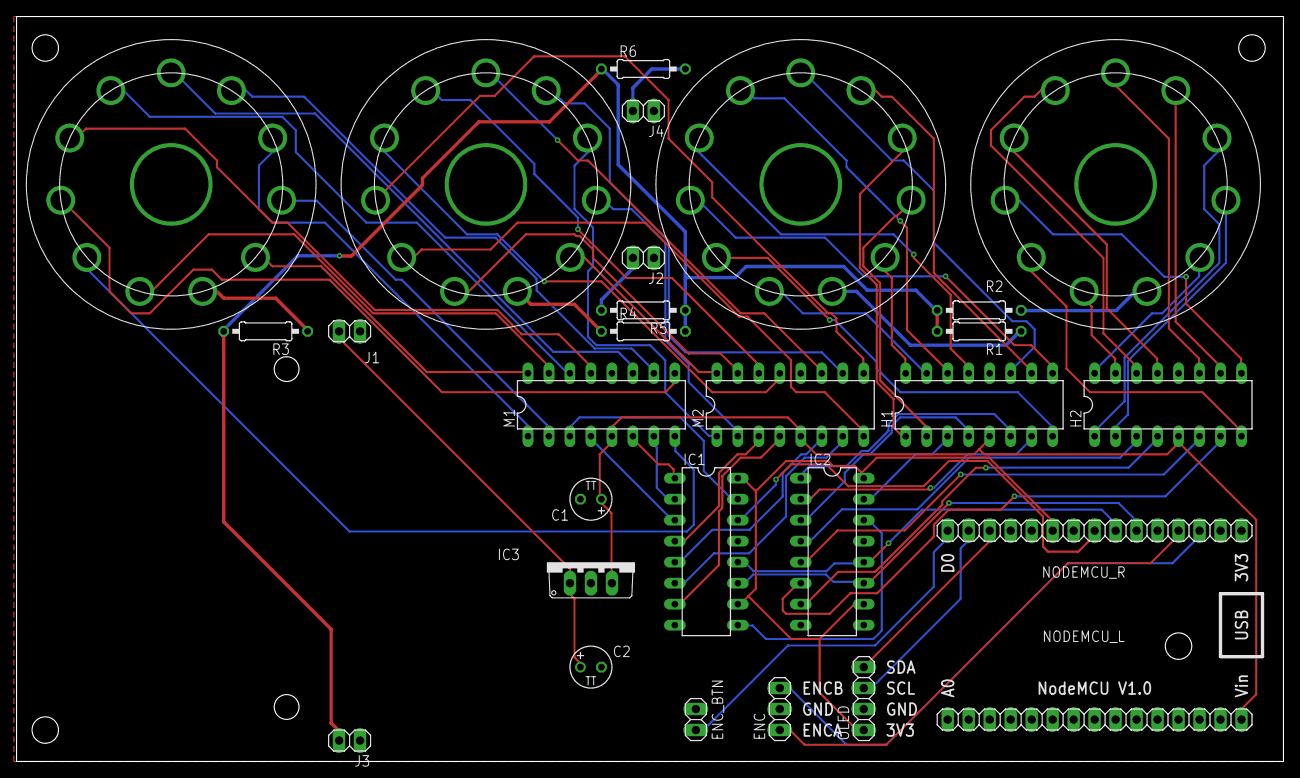
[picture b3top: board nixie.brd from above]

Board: 2 copper layers, 153.3 x 90.2 mm, 28 parts (0 on the bottom side), 76 nets.

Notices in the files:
parts and their libraries:
diy-modules: Released under the Creative Commons Attribution 4.0 International License: http://creativecommons.org/licenses/by/4.0
con-headers-jp: Copyright (C) 2008, Bob Starr
